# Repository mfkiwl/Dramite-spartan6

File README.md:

# Dramite

# Overall

This project aims to create a "bridge" that would work with a real 386SX processor. The full system should be IBM-PC compatible, being able to run operating system and software written for IBM-PC. Supporting for other CPUs (like 386DX, 486) and other architecture (like PC-98) are planned, but not now. This project also includes a software x86 emulator for the simulation purpose. Currently work in progress, see Progress for details.

# Build

To run the simulation:

```sh
cd rtl
make
cd ../sim
make
./sim
```

To build for the FPGA board:

Open the project file with ISE/Vivado/Quartus with corresponding FPGA project in the fpga folder. 

# Progress

RTL side:

 - [x] CPU interface
 - [ ] DDR memory controller interface
 - [ ] On-chip / Off-chip cache
 - [ ] 8042-compatible keyboard & mouse controller
 - [ ] 8259-compatible programmable interrupt controller
 - [ ] 8253-compatible programmable interval timer
 - [ ] 8250-compatible UART
 - [ ] MC146818-compatible RTC 
 - [ ] CPU-to-ISA bridge
 - [ ] VGA-compatible graphics

Board-specific:

 - [ ] PCF8583 RTC driver

Verilated Simulator:

 - [x] Basic memory support
 - [ ] x86 CPU simulation
 - [ ] VGA monitor
 - [ ] Serial console

# Acknowledge

This project use the "tiny x86 cpu emulator" by tuz358 (https://github.com/tuz358/cpu-emulator). This allowed simulation without a real CPU.

# Copyright

Unless otherwise noted, all HDL files are licensed under OHDL, all software codes including verilated simulation codes are licensed under GNU GPLv3.

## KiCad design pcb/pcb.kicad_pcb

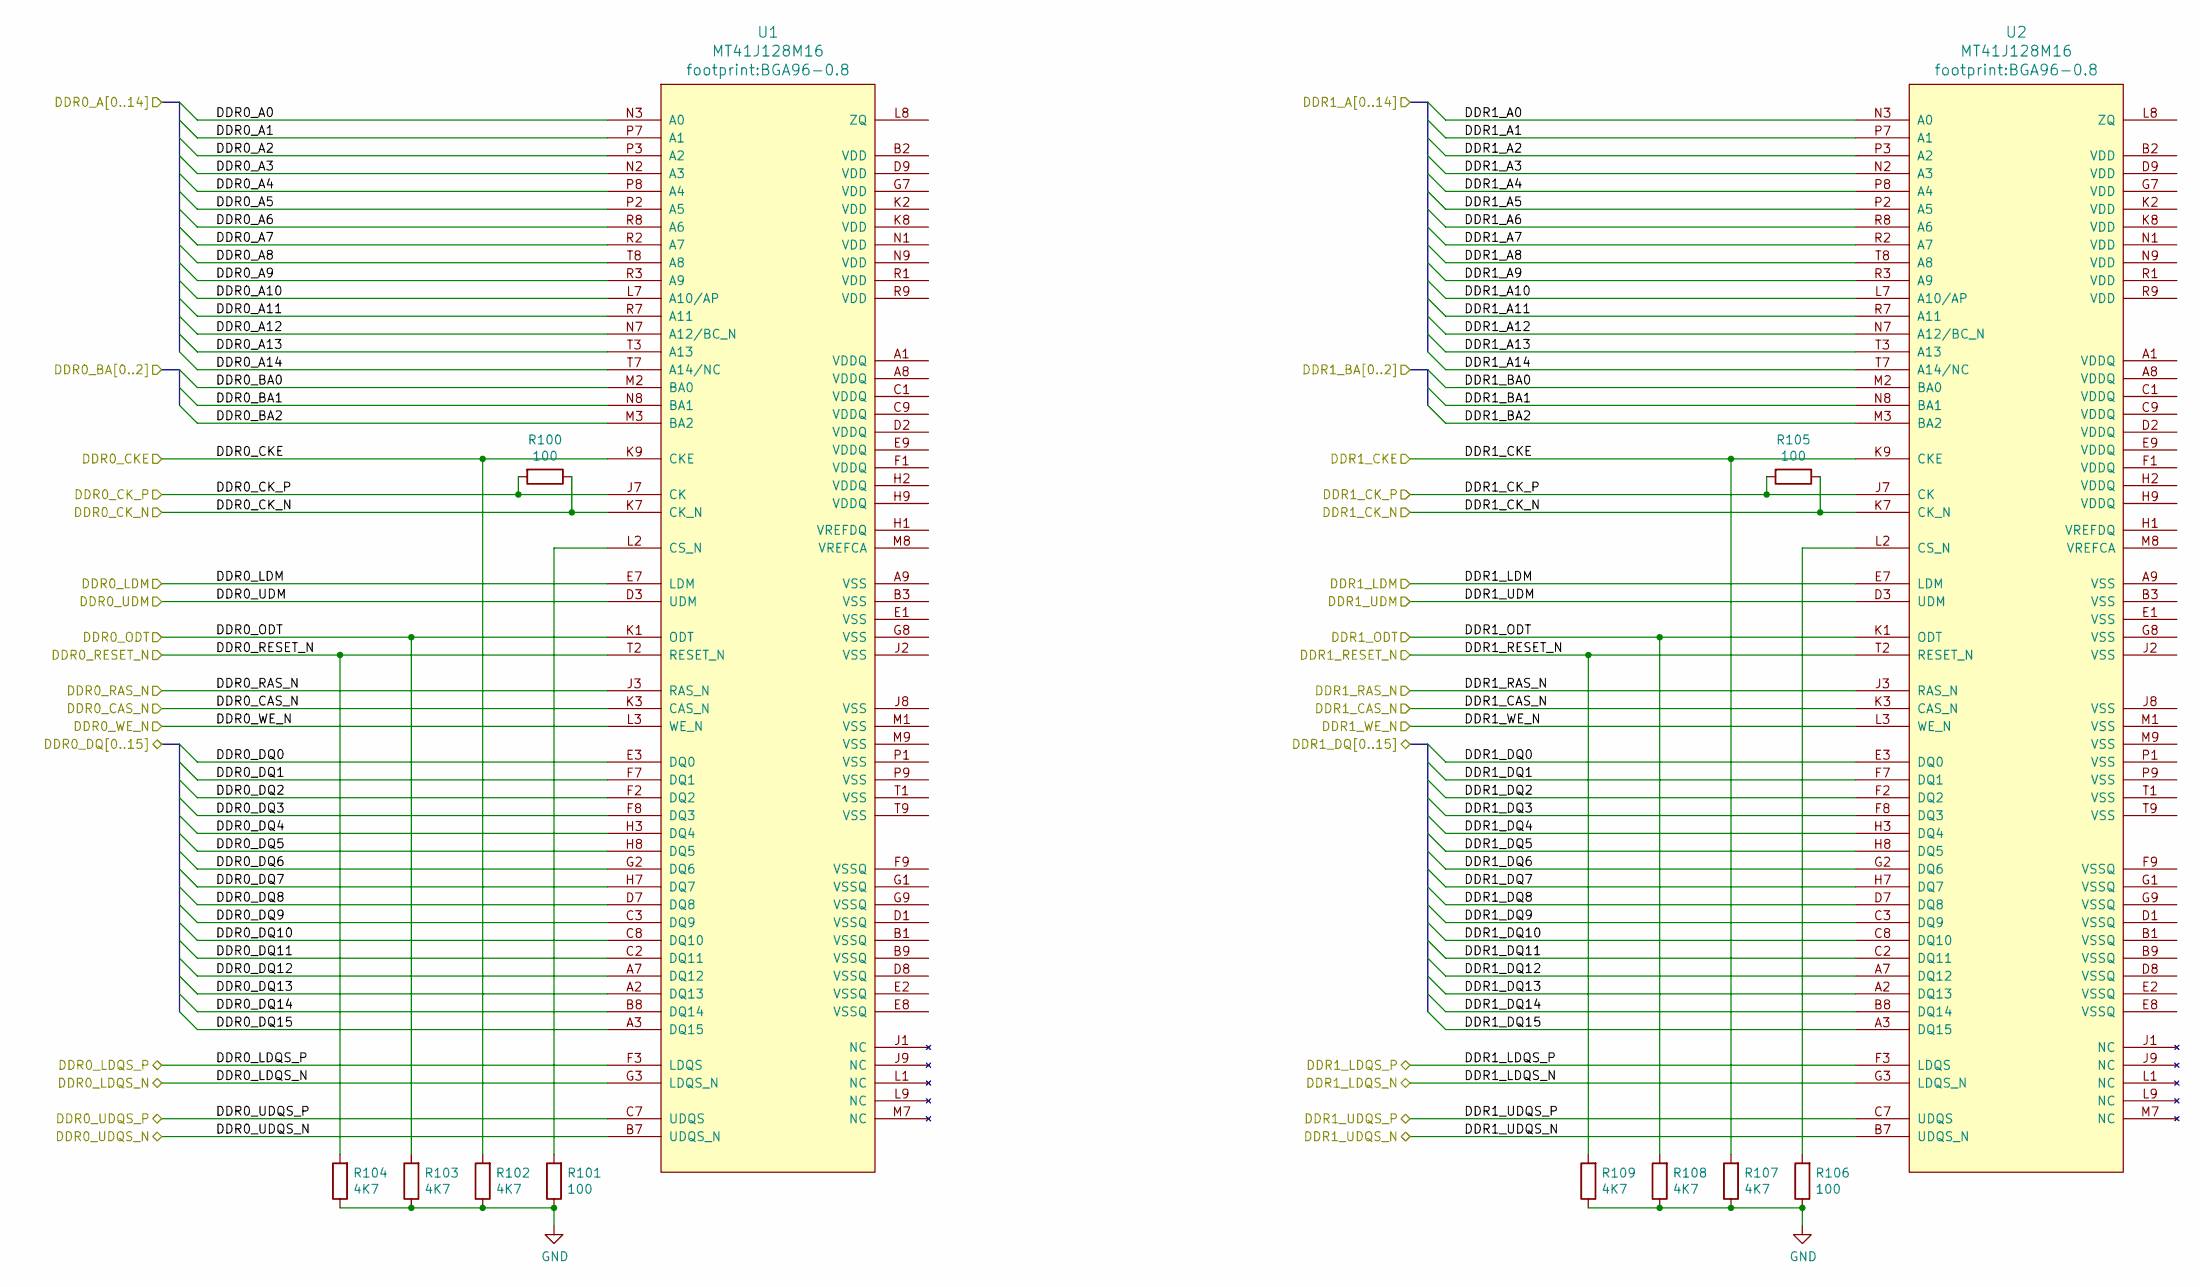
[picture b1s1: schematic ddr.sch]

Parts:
R100, R101, R105, R106: 100; R_0402_1005Metric
R102, R103, R104, R107, R108, R109: 4K7; R_0402_1005Metric
U1, U2: MT41J128M16; BGA96-0.8

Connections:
/ddr/DDR0_A0: U1.N3 (A0); also elsewhere on the board
/ddr/DDR0_A1: U1.P7 (A1); also elsewhere on the board
/ddr/DDR0_A2: U1.P3 (A2); also elsewhere on the board
/ddr/DDR0_A3: U1.N2 (A3); also elsewhere on the board
/ddr/DDR0_A4: U1.P8 (A4); also elsewhere on the board
/ddr/DDR0_A5: U1.P2 (A5); also elsewhere on the board
/ddr/DDR0_A6: U1.R8 (A6); also elsewhere on the board
/ddr/DDR0_A7: U1.R2 (A7); also elsewhere on the board
/ddr/DDR0_A8: U1.T8 (A8); also elsewhere on the board
/ddr/DDR0_A9: U1.R3 (A9); also elsewhere on the board
/ddr/DDR0_A10: U1.L7 (A10/AP); also elsewhere on the board
/ddr/DDR0_A11: U1.R7 (A11); also elsewhere on the board
/ddr/DDR0_A12: U1.N7 (A12/BC_N); also elsewhere on the board
/ddr/DDR0_A13: U1.T3 (A13); also elsewhere on the board
/ddr/DDR0_A14: U1.T7 (A14/NC); also elsewhere on the board
/ddr/DDR0_BA0: U1.M2 (BA0); also elsewhere on the board
/ddr/DDR0_BA1: U1.N8 (BA1); also elsewhere on the board
/ddr/DDR0_BA2: U1.M3 (BA2); also elsewhere on the board
/ddr/DDR0_CAS_N: U1.K3 (CAS_N); also elsewhere on the board
/ddr/DDR0_CKE: R102.2, U1.K9 (CKE); also elsewhere on the board
/ddr/DDR0_CK_N: R100.1, U1.K7 (CK_N); also elsewhere on the board
/ddr/DDR0_CK_P: R100.2, U1.J7 (CK); also elsewhere on the board
/ddr/DDR0_DQ0: U1.E3 (DQ0); also elsewhere on the board
/ddr/DDR0_DQ1: U1.F7 (DQ1); also elsewhere on the board
/ddr/DDR0_DQ2: U1.F2 (DQ2); also elsewhere on the board
/ddr/DDR0_DQ3: U1.F8 (DQ3); also elsewhere on the board
/ddr/DDR0_DQ4: U1.H3 (DQ4); also elsewhere on the board
/ddr/DDR0_DQ5: U1.H8 (DQ5); also elsewhere on the board
/ddr/DDR0_DQ6: U1.G2 (DQ6); also elsewhere on the board
/ddr/DDR0_DQ7: U1.H7 (DQ7); also elsewhere on the board
/ddr/DDR0_DQ8: U1.D7 (DQ8); also elsewhere on the board
/ddr/DDR0_DQ9: U1.C3 (DQ9); also elsewhere on the board
/ddr/DDR0_DQ10: U1.C8 (DQ10); also elsewhere on the board
/ddr/DDR0_DQ11: U1.C2 (DQ11); also elsewhere on the board
/ddr/DDR0_DQ12: U1.A7 (DQ12); also elsewhere on the board
/ddr/DDR0_DQ13: U1.A2 (DQ13); also elsewhere on the board
/ddr/DDR0_DQ14: U1.B8 (DQ14); also elsewhere on the board
/ddr/DDR0_DQ15: U1.A3 (DQ15); also elsewhere on the board
/ddr/DDR0_LDM: U1.E7 (LDM); also elsewhere on the board
/ddr/DDR0_LDQS_N: U1.G3 (LDQS_N); also elsewhere on the board
/ddr/DDR0_LDQS_P: U1.F3 (LDQS); also elsewhere on the board
/ddr/DDR0_ODT: R103.2, U1.K1 (ODT); also elsewhere on the board
/ddr/DDR0_RAS_N: U1.J3 (RAS_N); also elsewhere on the board
/ddr/DDR0_RESET_N: R104.2, U1.T2 (RESET_N); also elsewhere on the board
/ddr/DDR0_UDM: U1.D3 (UDM); also elsewhere on the board
/ddr/DDR0_UDQS_N: U1.B7 (UDQS_N); also elsewhere on the board
/ddr/DDR0_UDQS_P: U1.C7 (UDQS); also elsewhere on the board
/ddr/DDR0_WE_N: U1.L3 (WE_N); also elsewhere on the board
/ddr/DDR1_A0: U2.N3 (A0); also elsewhere on the board
/ddr/DDR1_A1: U2.P7 (A1); also elsewhere on the board
/ddr/DDR1_A2: U2.P3 (A2); also elsewhere on the board
/ddr/DDR1_A3: U2.N2 (A3); also elsewhere on the board
/ddr/DDR1_A4: U2.P8 (A4); also elsewhere on the board
/ddr/DDR1_A5: U2.P2 (A5); also elsewhere on the board
/ddr/DDR1_A6: U2.R8 (A6); also elsewhere on the board
/ddr/DDR1_A7: U2.R2 (A7); also elsewhere on the board
/ddr/DDR1_A8: U2.T8 (A8); also elsewhere on the board
/ddr/DDR1_A9: U2.R3 (A9); also elsewhere on the board
/ddr/DDR1_A10: U2.L7 (A10/AP); also elsewhere on the board
/ddr/DDR1_A11: U2.R7 (A11); also elsewhere on the board
/ddr/DDR1_A12: U2.N7 (A12/BC_N); also elsewhere on the board
/ddr/DDR1_A13: U2.T3 (A13); also elsewhere on the board
/ddr/DDR1_A14: U2.T7 (A14/NC); also elsewhere on the board
/ddr/DDR1_BA0: U2.M2 (BA0); also elsewhere on the board
/ddr/DDR1_BA1: U2.N8 (BA1); also elsewhere on the board
/ddr/DDR1_BA2: U2.M3 (BA2); also elsewhere on the board
/ddr/DDR1_CAS_N: U2.K3 (CAS_N); also elsewhere on the board
/ddr/DDR1_CKE: R107.2, U2.K9 (CKE); also elsewhere on the board
/ddr/DDR1_CK_N: R105.1, U2.K7 (CK_N); also elsewhere on the board
/ddr/DDR1_CK_P: R105.2, U2.J7 (CK); also elsewhere on the board
/ddr/DDR1_DQ0: U2.E3 (DQ0); also elsewhere on the board
/ddr/DDR1_DQ1: U2.F7 (DQ1); also elsewhere on the board
/ddr/DDR1_DQ2: U2.F2 (DQ2); also elsewhere on the board
/ddr/DDR1_DQ3: U2.F8 (DQ3); also elsewhere on the board
/ddr/DDR1_DQ4: U2.H3 (DQ4); also elsewhere on the board
/ddr/DDR1_DQ5: U2.H8 (DQ5); also elsewhere on the board
/ddr/DDR1_DQ6: U2.G2 (DQ6); also elsewhere on the board
/ddr/DDR1_DQ7: U2.H7 (DQ7); also elsewhere on the board
/ddr/DDR1_DQ8: U2.D7 (DQ8); also elsewhere on the board
/ddr/DDR1_DQ9: U2.C3 (DQ9); also elsewhere on the board
/ddr/DDR1_DQ10: U2.C8 (DQ10); also elsewhere on the board
/ddr/DDR1_DQ11: U2.C2 (DQ11); also elsewhere on the board
/ddr/DDR1_DQ12: U2.A7 (DQ12); also elsewhere on the board
/ddr/DDR1_DQ13: U2.A2 (DQ13); also elsewhere on the board
/ddr/DDR1_DQ14: U2.B8 (DQ14); also elsewhere on the board
/ddr/DDR1_DQ15: U2.A3 (DQ15); also elsewhere on the board
/ddr/DDR1_LDM: U2.E7 (LDM); also elsewhere on the board
/ddr/DDR1_LDQS_N: U2.G3 (LDQS_N); also elsewhere on the board
/ddr/DDR1_LDQS_P: U2.F3 (LDQS); also elsewhere on the board
/ddr/DDR1_ODT: R108.2, U2.K1 (ODT); also elsewhere on the board
/ddr/DDR1_RAS_N: U2.J3 (RAS_N); also elsewhere on the board
/ddr/DDR1_RESET_N: R109.2, U2.T2 (RESET_N); also elsewhere on the board
/ddr/DDR1_UDM: U2.D3 (UDM); also elsewhere on the board
/ddr/DDR1_UDQS_N: U2.B7 (UDQS_N); also elsewhere on the board
/ddr/DDR1_UDQS_P: U2.C7 (UDQS); also elsewhere on the board
/ddr/DDR1_WE_N: U2.L3 (WE_N); also elsewhere on the board
GND: R101.1, R102.1, R103.1, R104.1, R106.1, R107.1, R108.1, R109.1
unnamed: R101.2, U1.L2 (CS_N)
unnamed: R106.2, U2.L2 (CS_N)

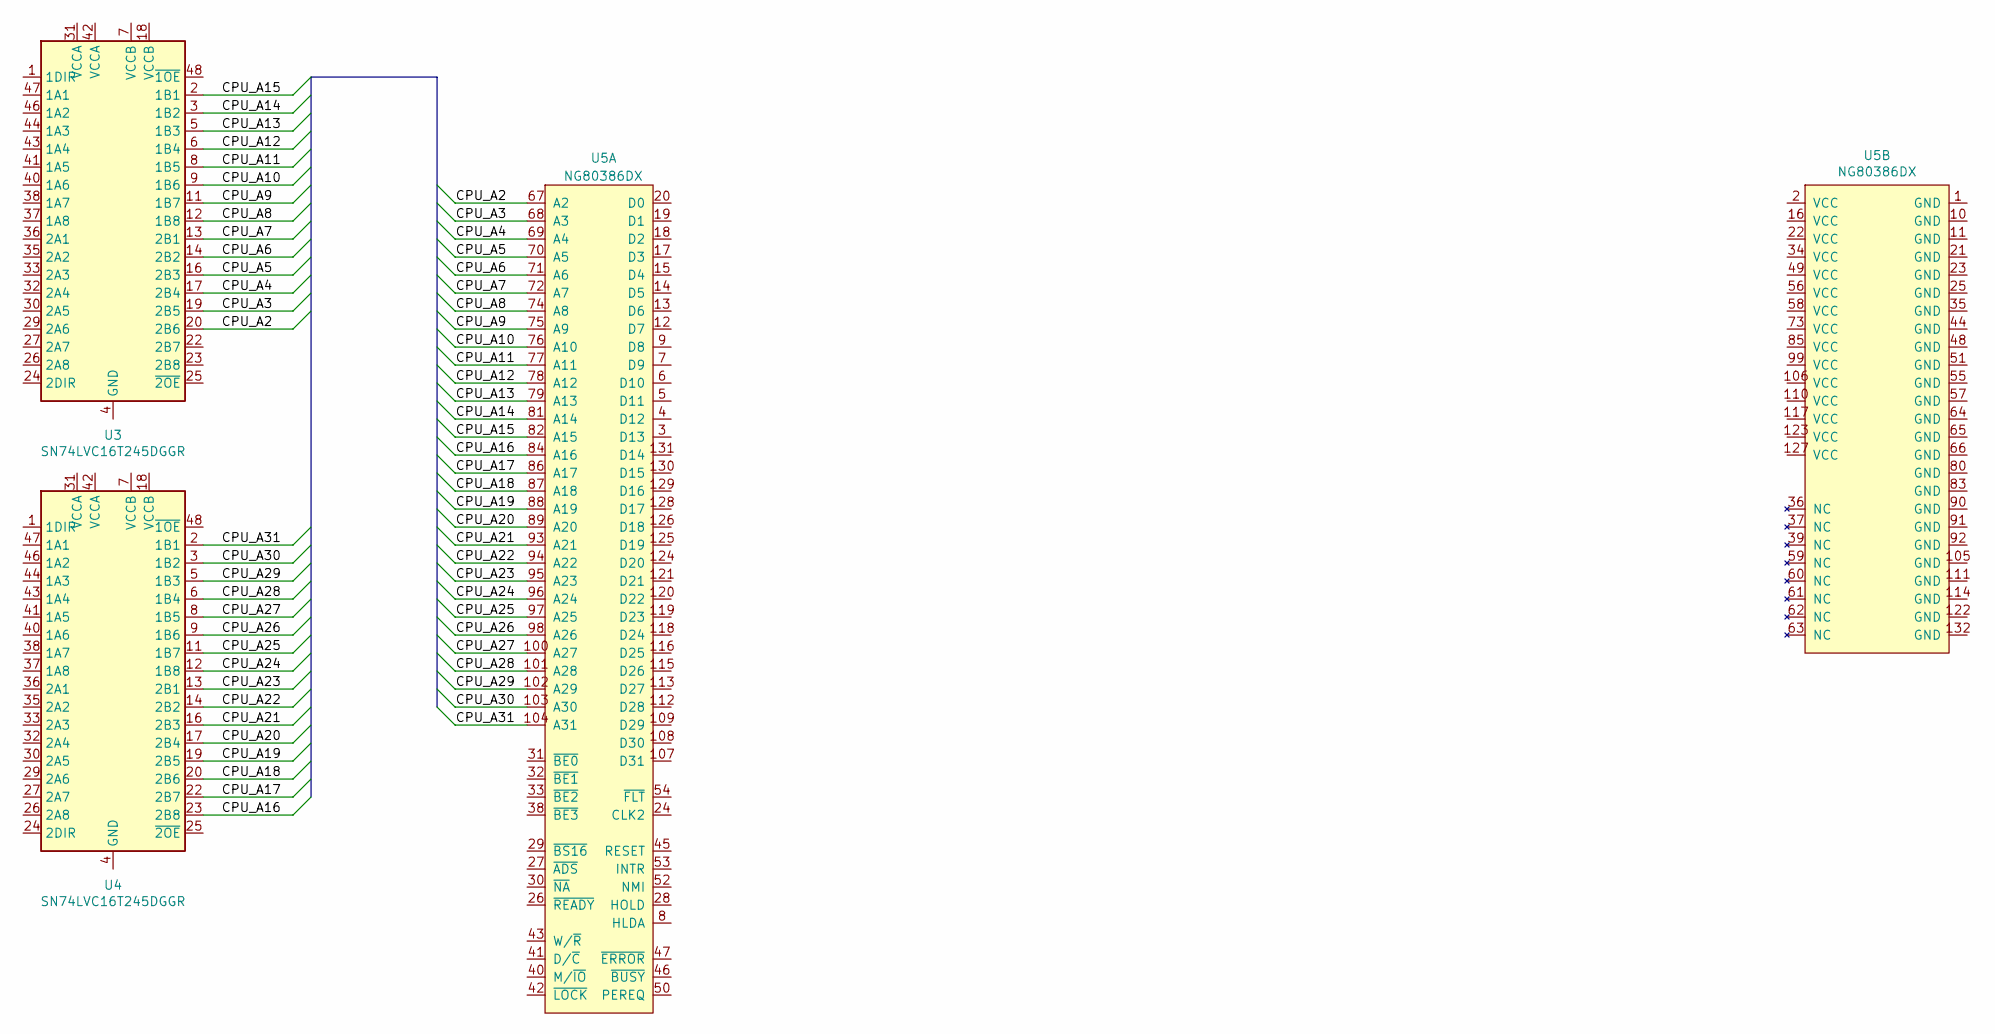
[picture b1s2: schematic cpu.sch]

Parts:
U3, U4: SN74LVC16T245DGGR; TSSOP-48_6.1x12.5mm_P0.5mm
U5: NG80386DX; PQFP-132_24x24mm_P0.635mm_i386

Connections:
/cpu/CPU_A2: U3.20 (2B6), U5.67 (A2)
/cpu/CPU_A3: U3.19 (2B5), U5.68 (A3)
/cpu/CPU_A4: U3.17 (2B4), U5.69 (A4)
/cpu/CPU_A5: U3.16 (2B3), U5.70 (A5)
/cpu/CPU_A6: U3.14 (2B2), U5.71 (A6)
/cpu/CPU_A7: U3.13 (2B1), U5.72 (A7)
/cpu/CPU_A8: U3.12 (1B8), U5.74 (A8)
/cpu/CPU_A9: U3.11 (1B7), U5.75 (A9)
/cpu/CPU_A10: U3.9 (1B6), U5.76 (A10)
/cpu/CPU_A11: U3.8 (1B5), U5.77 (A11)
/cpu/CPU_A12: U3.6 (1B4), U5.78 (A12)
/cpu/CPU_A13: U3.5 (1B3), U5.79 (A13)
/cpu/CPU_A14: U3.3 (1B2), U5.81 (A14)
/cpu/CPU_A15: U3.2 (1B1), U5.82 (A15)
/cpu/CPU_A16: U4.23 (2B8), U5.84 (A16)
/cpu/CPU_A17: U4.22 (2B7), U5.86 (A17)
/cpu/CPU_A18: U4.20 (2B6), U5.87 (A18)
/cpu/CPU_A19: U4.19 (2B5), U5.88 (A19)
/cpu/CPU_A20: U4.17 (2B4), U5.89 (A20)
/cpu/CPU_A21: U4.16 (2B3), U5.93 (A21)
/cpu/CPU_A22: U4.14 (2B2), U5.94 (A22)
/cpu/CPU_A23: U4.13 (2B1), U5.95 (A23)
/cpu/CPU_A24: U4.12 (1B8), U5.96 (A24)
/cpu/CPU_A25: U4.11 (1B7), U5.97 (A25)
/cpu/CPU_A26: U4.9 (1B6), U5.98 (A26)
/cpu/CPU_A27: U4.8 (1B5), U5.100 (A27)
/cpu/CPU_A28: U4.6 (1B4), U5.101 (A28)
/cpu/CPU_A29: U4.5 (1B3), U5.102 (A29)
/cpu/CPU_A30: U4.3 (1B2), U5.103 (A30)
/cpu/CPU_A31: U4.2 (1B1), U5.104 (A31)
unnamed: U3.4 (GND), U3.10 (GND), U3.15 (GND), U3.21 (GND), U3.28 (GND), U3.34 (GND), U3.45 (GND)
unnamed: U4.4 (GND), U4.10 (GND), U4.15 (GND), U4.21 (GND), U4.28 (GND), U4.34 (GND), U4.45 (GND)

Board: 2 copper layers, 16 parts (0 on the bottom side), 131 nets, no tracks yet.

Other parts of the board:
U200: XC6SLX45-FGG484; BGA-484_23.0x23.0mm_Layout22x22_P1.0mm

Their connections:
/ddr/DDR0_A0: U200.F21; also elsewhere on the board
/ddr/DDR0_A1: U200.F22; also elsewhere on the board
/ddr/DDR0_A2: U200.E22; also elsewhere on the board
/ddr/DDR0_A3: U200.G20; also elsewhere on the board
/ddr/DDR0_A4: U200.F20; also elsewhere on the board
/ddr/DDR0_A5: U200.K20; also elsewhere on the board
/ddr/DDR0_A6: U200.K19; also elsewhere on the board
/ddr/DDR0_A7: U200.E20; also elsewhere on the board
/ddr/DDR0_A8: U200.C20; also elsewhere on the board
/ddr/DDR0_A9: U200.C22; also elsewhere on the board
/ddr/DDR0_A10: U200.G19; also elsewhere on the board
/ddr/DDR0_A11: U200.F19; also elsewhere on the board
/ddr/DDR0_A12: U200.D22; also elsewhere on the board
/ddr/DDR0_A13: U200.D19; also elsewhere on the board
/ddr/DDR0_A14: U200.D20; also elsewhere on the board
/ddr/DDR0_BA0: U200.J17; also elsewhere on the board
/ddr/DDR0_BA1: U200.K17; also elsewhere on the board
/ddr/DDR0_BA2: U200.H18; also elsewhere on the board
/ddr/DDR0_CAS_N: U200.H22; also elsewhere on the board
/ddr/DDR0_CKE: U200.D21; also elsewhere on the board
/ddr/DDR0_CK_N: U200.J19; also elsewhere on the board
/ddr/DDR0_CK_P: U200.H20; also elsewhere on the board
/ddr/DDR0_DQ0: U200.N20; also elsewhere on the board
/ddr/DDR0_DQ1: U200.N22; also elsewhere on the board
/ddr/DDR0_DQ2: U200.M21; also elsewhere on the board
/ddr/DDR0_DQ3: U200.M22; also elsewhere on the board
/ddr/DDR0_DQ4: U200.J20; also elsewhere on the board
/ddr/DDR0_DQ5: U200.J22; also elsewhere on the board
/ddr/DDR0_DQ6: U200.K21; also elsewhere on the board
/ddr/DDR0_DQ7: U200.K22; also elsewhere on the board
/ddr/DDR0_DQ8: U200.P21; also elsewhere on the board
/ddr/DDR0_DQ9: U200.P22; also elsewhere on the board
/ddr/DDR0_DQ10: U200.R20; also elsewhere on the board
/ddr/DDR0_DQ11: U200.R22; also elsewhere on the board
/ddr/DDR0_DQ12: U200.U20; also elsewhere on the board
/ddr/DDR0_DQ13: U200.U22; also elsewhere on the board
/ddr/DDR0_DQ14: U200.V21; also elsewhere on the board
/ddr/DDR0_DQ15: U200.V22; also elsewhere on the board
/ddr/DDR0_LDM: U200.L19; also elsewhere on the board
/ddr/DDR0_LDQS_N: U200.L22; also elsewhere on the board
/ddr/DDR0_LDQS_P: U200.L20; also elsewhere on the board
/ddr/DDR0_ODT: U200.G22; also elsewhere on the board
/ddr/DDR0_RAS_N: U200.H21; also elsewhere on the board
/ddr/DDR0_RESET_N: U200.F18; also elsewhere on the board
/ddr/DDR0_UDM: U200.M20; also elsewhere on the board
/ddr/DDR0_UDQS_N: U200.T22; also elsewhere on the board
/ddr/DDR0_UDQS_P: U200.T21; also elsewhere on the board
/ddr/DDR0_WE_N: U200.H19; also elsewhere on the board
/ddr/DDR1_A0: U200.H2; also elsewhere on the board
/ddr/DDR1_A1: U200.H1; also elsewhere on the board
/ddr/DDR1_A2: U200.H5; also elsewhere on the board
/ddr/DDR1_A3: U200.K6; also elsewhere on the board
/ddr/DDR1_A4: U200.F3; also elsewhere on the board
/ddr/DDR1_A5: U200.K3; also elsewhere on the board
/ddr/DDR1_A6: U200.J4; also elsewhere on the board
/ddr/DDR1_A7: U200.H6; also elsewhere on the board
/ddr/DDR1_A8: U200.E3; also elsewhere on the board
/ddr/DDR1_A9: U200.E1; also elsewhere on the board
/ddr/DDR1_A10: U200.G4; also elsewhere on the board
/ddr/DDR1_A11: U200.C1; also elsewhere on the board
/ddr/DDR1_A12: U200.D1; also elsewhere on the board
/ddr/DDR1_A13: U200.G6; also elsewhere on the board
/ddr/DDR1_A14: U200.F5; also elsewhere on the board
/ddr/DDR1_BA0: U200.G3; also elsewhere on the board
/ddr/DDR1_BA1: U200.G1; also elsewhere on the board
/ddr/DDR1_BA2: U200.F1; also elsewhere on the board
/ddr/DDR1_CAS_N: U200.K4; also elsewhere on the board
/ddr/DDR1_CKE: U200.D2; also elsewhere on the board
/ddr/DDR1_CK_N: U200.H3; also elsewhere on the board
/ddr/DDR1_CK_P: U200.H4; also elsewhere on the board
/ddr/DDR1_DQ0: U200.N3; also elsewhere on the board
/ddr/DDR1_DQ1: U200.N1; also elsewhere on the board
/ddr/DDR1_DQ2: U200.M2; also elsewhere on the board
/ddr/DDR1_DQ3: U200.M1; also elsewhere on the board
/ddr/DDR1_DQ4: U200.J3; also elsewhere on the board
/ddr/DDR1_DQ5: U200.J1; also elsewhere on the board
/ddr/DDR1_DQ6: U200.K2; also elsewhere on the board
/ddr/DDR1_DQ7: U200.K1; also elsewhere on the board
/ddr/DDR1_DQ8: U200.P2; also elsewhere on the board
/ddr/DDR1_DQ9: U200.P1; also elsewhere on the board
/ddr/DDR1_DQ10: U200.R3; also elsewhere on the board
/ddr/DDR1_DQ11: U200.R1; also elsewhere on the board
/ddr/DDR1_DQ12: U200.U3; also elsewhere on the board
/ddr/DDR1_DQ13: U200.U1; also elsewhere on the board
/ddr/DDR1_DQ14: U200.V2; also elsewhere on the board
/ddr/DDR1_DQ15: U200.V1; also elsewhere on the board
/ddr/DDR1_LDM: U200.L4; also elsewhere on the board
/ddr/DDR1_LDQS_N: U200.L1; also elsewhere on the board
/ddr/DDR1_LDQS_P: U200.L3; also elsewhere on the board
/ddr/DDR1_ODT: U200.J6; also elsewhere on the board
/ddr/DDR1_RAS_N: U200.K5; also elsewhere on the board
/ddr/DDR1_RESET_N: U200.C3; also elsewhere on the board
/ddr/DDR1_UDM: U200.M3; also elsewhere on the board
/ddr/DDR1_UDQS_N: U200.T1; also elsewhere on the board
/ddr/DDR1_UDQS_P: U200.T2; also elsewhere on the board
/ddr/DDR1_WE_N: U200.F2; also elsewhere on the board

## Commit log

2018-09-15 rtl: bus master skeleton
2018-09-16 fpga: initial ml505 port
2018-09-16 readme: update
2018-09-16 readme: fix style and add info
2018-09-22 sim: start working on simulation
2018-09-22 rtl: fix verilator build
2018-09-30 sim: working on cpu simulation
2019-11-16 sim: implement basic bus request
2019-11-17 rtl: sepearate cpu interface out
2019-11-17 test: add simple cpu test programs
2019-11-20 pcb: start working on pcb
